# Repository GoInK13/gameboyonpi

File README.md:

# gameboyonpi

PCB in kicad directory.
Teensy software for joystick, mouse and media keyboard.

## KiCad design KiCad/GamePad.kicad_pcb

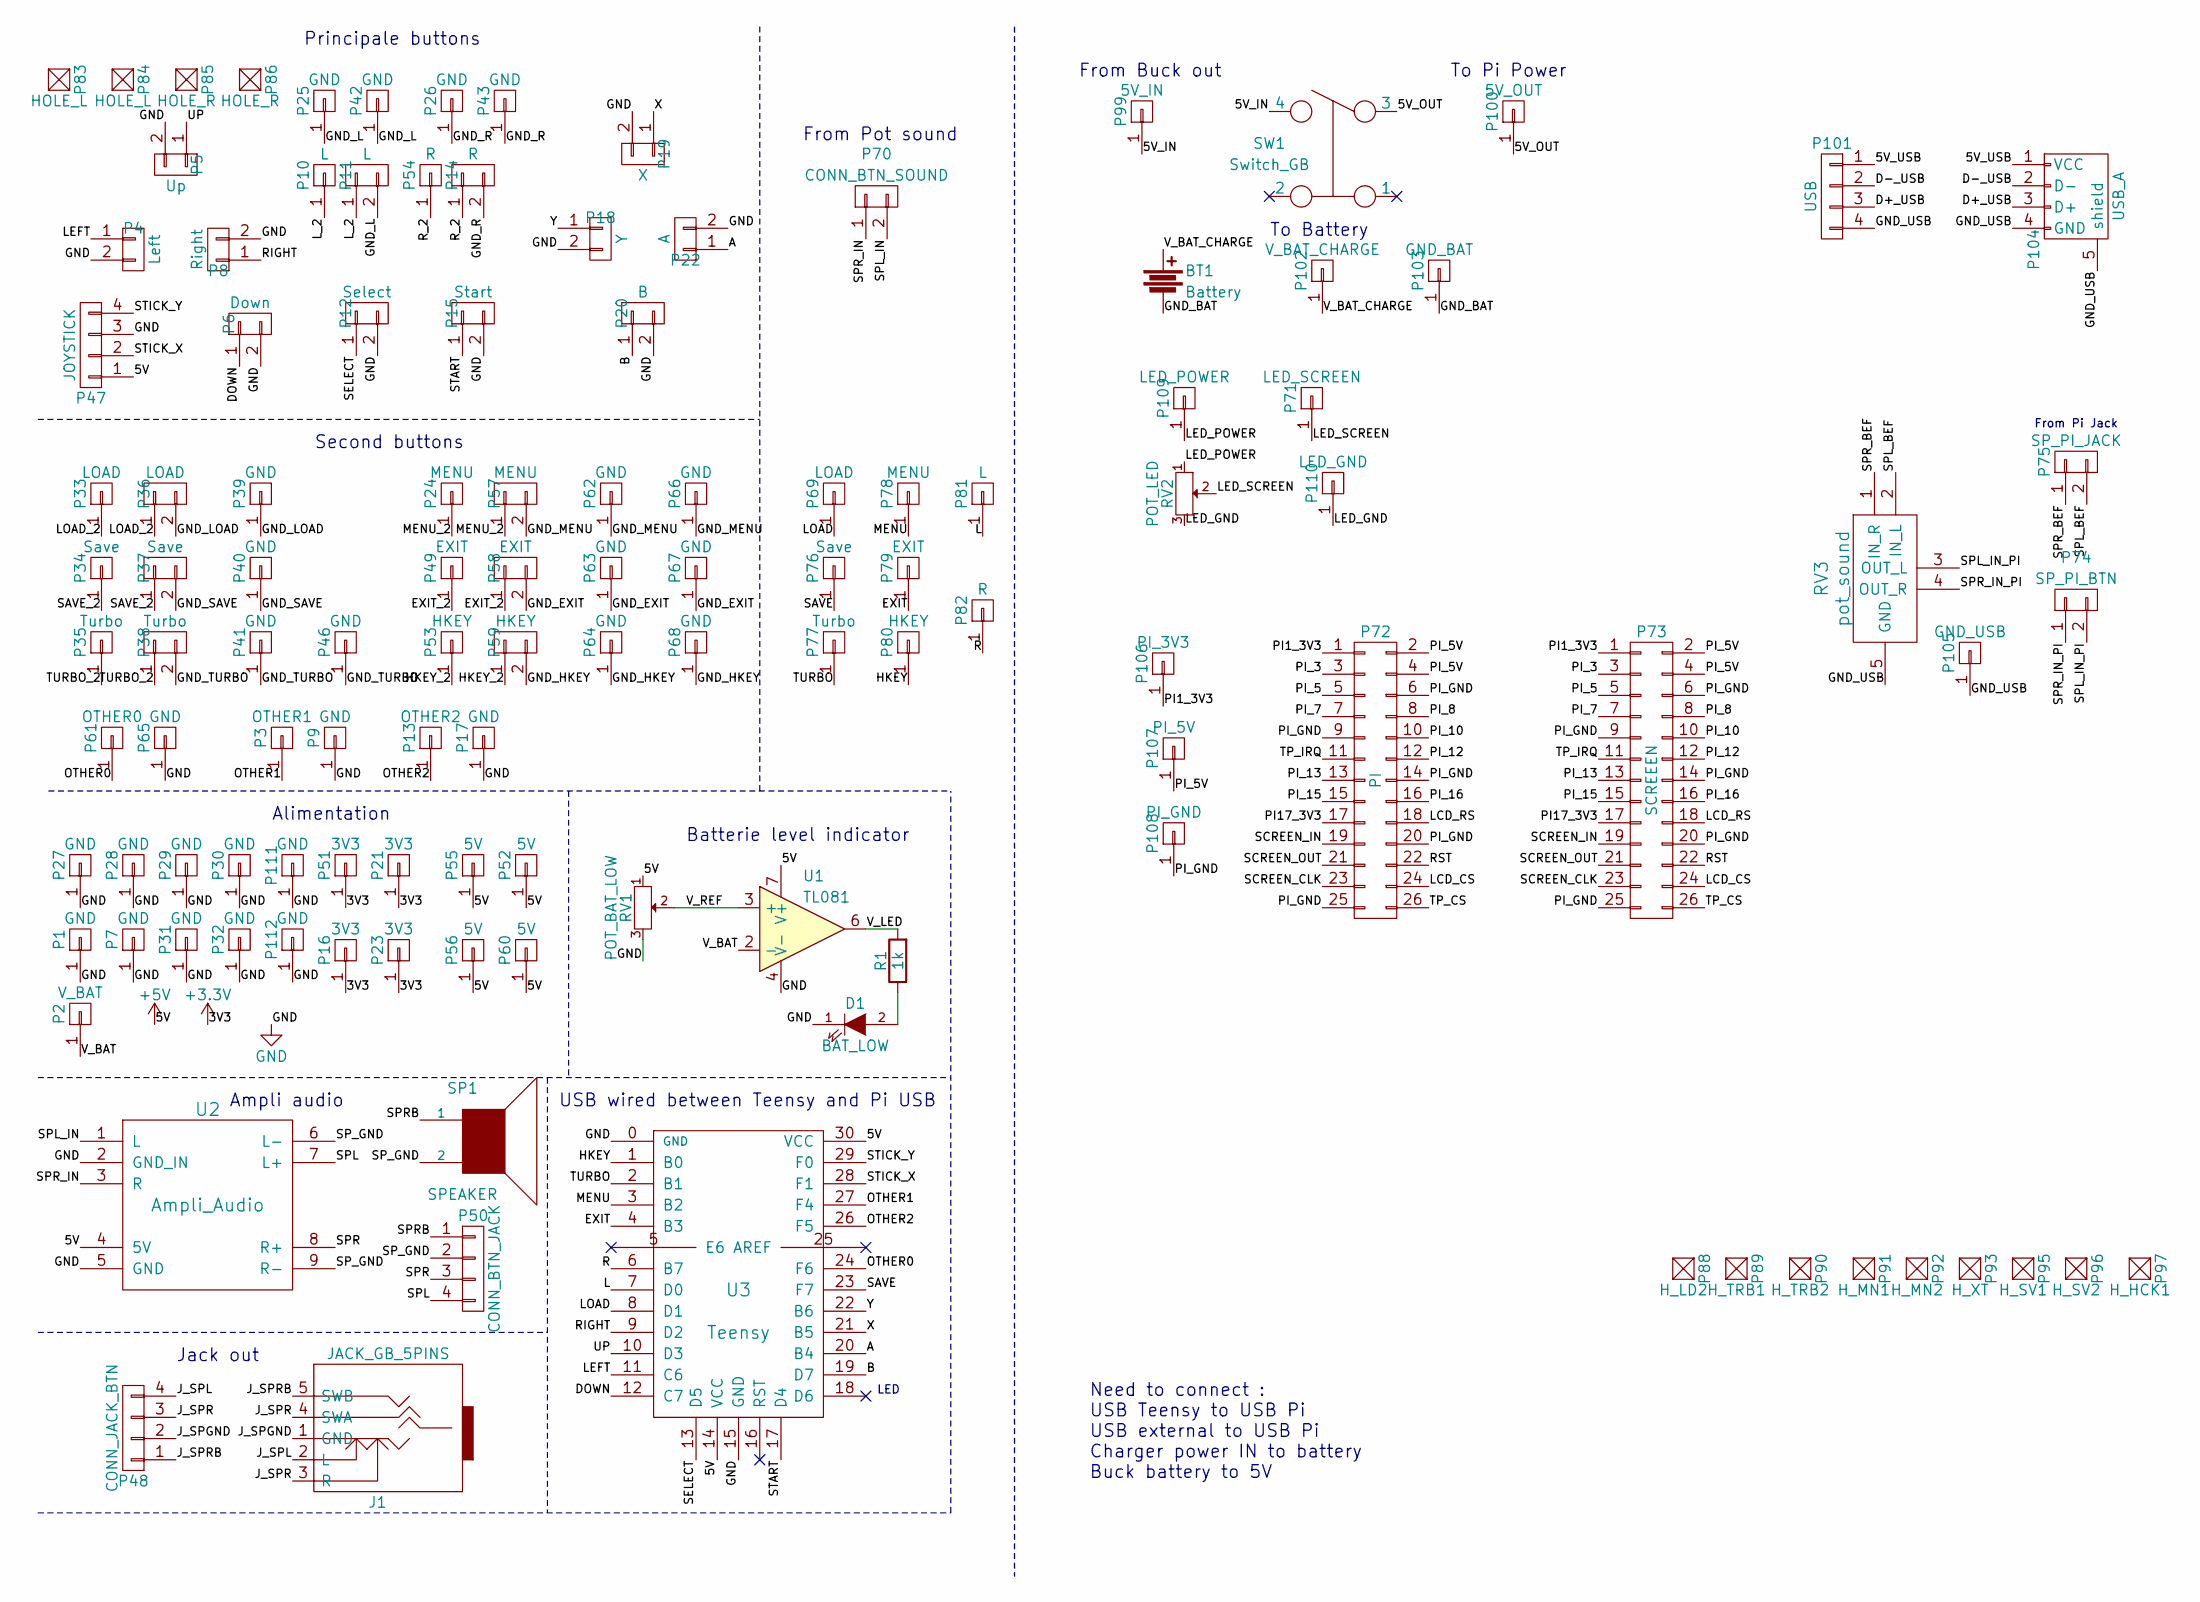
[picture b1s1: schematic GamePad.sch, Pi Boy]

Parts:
BT1: Battery; charger_bat
D1: BAT_LOW; LED-3MM
J1: JACK_GB_5PINS; Jack
P1, P7, P9, P17, P25, P26, P27, P28, P29, P30, P31, P32, P39, P40, P41, P42, P43, P46, P62, P63, P64, P65, P66, P67, P68, P111, P112: GND; header_1-2
P2: V_BAT; header_1-2
P3: OTHER1; header_1-2
P4: Left; button_round
P5: Up; button_round
P6: Down; button_round
P8: Right; button_round
P10, P81: L; header_1-2
P11: L; button_rectangle
P12: Select; button_rectangle
P13: OTHER2; header_1-2
P14: R; button_rectangle
P15: Start; button_rectangle
P16, P21, P23, P51: 3V3; header_1-2
P18: Y; button_round
P19: X; button_round
P20: B; button_round
P22: A; button_round
P24, P78: MENU; header_1-2
P33, P69: LOAD; header_1-2
P34, P76: Save; header_1-2
P35, P77: Turbo; header_1-2
P36: LOAD; button_round
P37: Save; button_round
P38: Turbo; button_round
P47: JOYSTICK; PSP_Joystick
P48: CONN_JACK_BTN; Pin_Header_Straight_1x04
P49, P79: EXIT; header_1-2
P50: CONN_BTN_JACK; Pin_Header_Straight_1x04
P52, P55, P56, P60: 5V; header_1-2
P53, P80: HKEY; header_1-2
P54, P82: R; header_1-2
P57: MENU; button_round
P58: EXIT; button_round
P59: HKEY; button_round
P61: OTHER0; header_1-2
P70: CONN_BTN_SOUND; Pin_Header_Straight_1x02
P71: LED_SCREEN; header_1-2
P72: PI; Socket_Strip_Straight_2x20
P73: SCREEEN; Socket_Strip_Straight_2x13
P74: SP_PI_BTN; Socket_Strip_Straight_1x02
P75: SP_PI_JACK; Pin_Header_Straight_1x02
P83, P84: HOLE_L; Hole_1mm
P85, P86: HOLE_R; Hole_1mm
P88: H_LD2; Hole_1mm
P89: H_TRB1; Hole_1mm
P90: H_TRB2; Hole_1mm
P91: H_MN1; Hole_1mm
P92: H_MN2; Hole_1mm
P93: H_XT; Hole_1mm
P95: H_SV1; Hole_1mm
P96: H_SV2; Hole_1mm
P97: H_HCK1; Hole_1mm
P99: 5V_IN; header_1-2
P100: 5V_OUT; header_1-2
P101: USB; Pin_Header_Straight_1x04
P102: V_BAT_CHARGE; header_1-2
P103: GND_BAT; header_1-2
P104: USB_A
P105: GND_USB; header_1-2
P106: PI_3V3; header_1-2
P107: PI_5V; header_1-2
P108: PI_GND; header_1-2
P109: LED_POWER; header_1-2
P110: LED_GND; header_1-2
R1: 1k; Resistor_Horizontal_RM10mm
RV1: POT_BAT_LOW; RV2X4
RV2: POT_LED; pot_screen
RV3: pot_sound
SP1: SPEAKER; Pin_Header_Straight_1x02
SW1: Switch_GB
U1: TL081; PDIP-8
U2: Ampli_Audio; ampli_audio
U3: Teensy

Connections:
+3V3: P16.1, P21.1, P23.1, P51.1
+5V: P47.1, P52.1, P55.1, P56.1, P60.1, RV1.1, U1.7 (V+), U2.4 (5V), U3.14 (VCC), U3.30 (VCC)
/5V_IN: P99.1, SW1.4
/5V_OUT: P100.1, SW1.3
/5V_USB: P101.1, P104.1 (VCC)
/A: P22.1, U3.20 (B4)
/B: P20.1, U3.19 (D7)
/D+_USB: P101.3, P104.3 (D+)
/D-_USB: P101.2, P104.2 (D-)
/DOWN: P6.1, U3.12 (C7)
/EXIT: P79.1, U3.4 (B3)
/EXIT_2: P49.1, P58.1
/GND_BAT: BT1.2, P103.1
/GND_EXIT: P58.2, P63.1, P67.1
/GND_HKEY: P59.2, P64.1, P68.1
/GND_L: P11.2, P25.1, P42.1
/GND_LOAD: P36.2, P39.1
/GND_MENU: P57.2, P62.1, P66.1
/GND_R: P14.2, P26.1, P43.1
/GND_SAVE: P37.2, P40.1
/GND_TURBO: P38.2, P41.1, P46.1
/GND_USB: P101.4, P104.4 (GND), P104.5 (shield), P105.1, RV3.5 (GND)
/HKEY: P80.1, U3.1 (B0)
/HKEY_2: P53.1, P59.1
/J_SPGND: J1.1 (GND), P48.2
/J_SPL: J1.2 (L), P48.4
/J_SPR: J1.3 (R), J1.4 (SWA), P48.3
/J_SPRB: J1.5 (SWB), P48.1
/L: P81.1, U3.7 (D0)
/LCD_CS: P72.24, P73.24
/LCD_RS: P72.18, P73.18
/LED_GND: P110.1, RV2.3
/LED_POWER: P109.1, RV2.1
/LED_SCREEN: P71.1, RV2.2
/LEFT: P4.1, U3.11 (C6)
/LOAD: P69.1, U3.8 (D1)
/LOAD_2: P33.1, P36.1
/L_2: P10.1, P11.1
/MENU: P78.1, U3.3 (B2)
/MENU_2: P24.1, P57.1
/OTHER0: P61.1, U3.24 (F6)
/OTHER1: P3.1, U3.27 (F4)
/OTHER2: P13.1, U3.26 (F5)
/PI1_3V3: P72.1, P73.1, P106.1
/PI17_3V3: P72.17, P73.17
/PI_3: P72.3, P73.3
/PI_5: P72.5, P73.5
/PI_5V: P72.2, P72.4, P73.2, P73.4, P107.1
/PI_7: P72.7, P73.7
/PI_8: P72.8, P73.8
/PI_10: P72.10, P73.10
/PI_12: P72.12, P73.12
/PI_13: P72.13, P73.13
/PI_15: P72.15, P73.15
/PI_16: P72.16, P73.16
/PI_GND: P72.6, P72.9, P72.14, P72.20, P72.25, P73.6, P73.9, P73.14, P73.20, P73.25, P108.1
/R: P82.1, U3.6 (B7)
/RIGHT: P8.1, U3.9 (D2)
/RST: P72.22, P73.22
/R_2: P14.1, P54.1
/SAVE: P76.1, U3.23 (F7)
/SAVE_2: P34.1, P37.1
/SCREEN_CLK: P72.23, P73.23
/SCREEN_IN: P72.19, P73.19
/SCREEN_OUT: P72.21, P73.21
/SELECT: P12.1, U3.13 (D5)
/SPL: P50.4, U2.7 (L+)
/SPL_BEF: P75.2, RV3.2 (IN_L)
/SPL_IN: P70.2, U2.1 (L)
/SPL_IN_PI: P74.2, RV3.3 (OUT_L)
/SPR: P50.3, U2.8 (R+)
/SPRB: P50.1, SP1.1
/SPR_BEF: P75.1, RV3.1 (IN_R)
/SPR_IN: P70.1, U2.3 (R)
/SPR_IN_PI: P74.1, RV3.4 (OUT_R)
/SP_GND: P50.2, SP1.2, U2.6 (L-), U2.9 (R-)
/START: P15.1, U3.17 (D4)
/STICK_X: P47.2, U3.28 (F1)
/STICK_Y: P47.4, U3.29 (F0)
/TP_CS: P72.26, P73.26
/TP_IRQ: P72.11, P73.11
/TURBO: P77.1, U3.2 (B1)
/TURBO_2: P35.1, P38.1
/UP: P5.1, U3.10 (D3)
/V_BAT: P2.1, U1.2 (-)
/V_BAT_CHARGE: BT1.1, P102.1
/V_LED: R1.2, U1.6
/V_REF: RV1.2, U1.3 (+)
/X: P19.1, U3.21 (B5)
/Y: P18.1, U3.22 (B6)
GND: D1.1 (K), P1.1, P4.2, P5.2, P6.2, P7.1, P8.2, P9.1, P12.2, P15.2, P17.1, P18.2, P19.2, P20.2, P22.2, P27.1, P28.1, P29.1, P30.1, P31.1, P32.1, P47.3, P65.1, P111.1, P112.1, RV1.3, U1.4 (V-), U2.2 (GND_IN), U2.5 (GND), U3.0 (GND), U3.15 (GND)
unnamed: D1.2 (A), R1.1

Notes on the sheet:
USB wired between Teensy and Pi USB
LED
From Pi Jack
Alimentation
Principale buttons
Second buttons
Ampli audio
Jack out
Batterie level indicator
Need to connect : USB Teensy to USB Pi USB external to USB Pi Charger power IN to battery Buck battery to 5V
From Buck out
To Pi Power
To Battery
From Pot sound

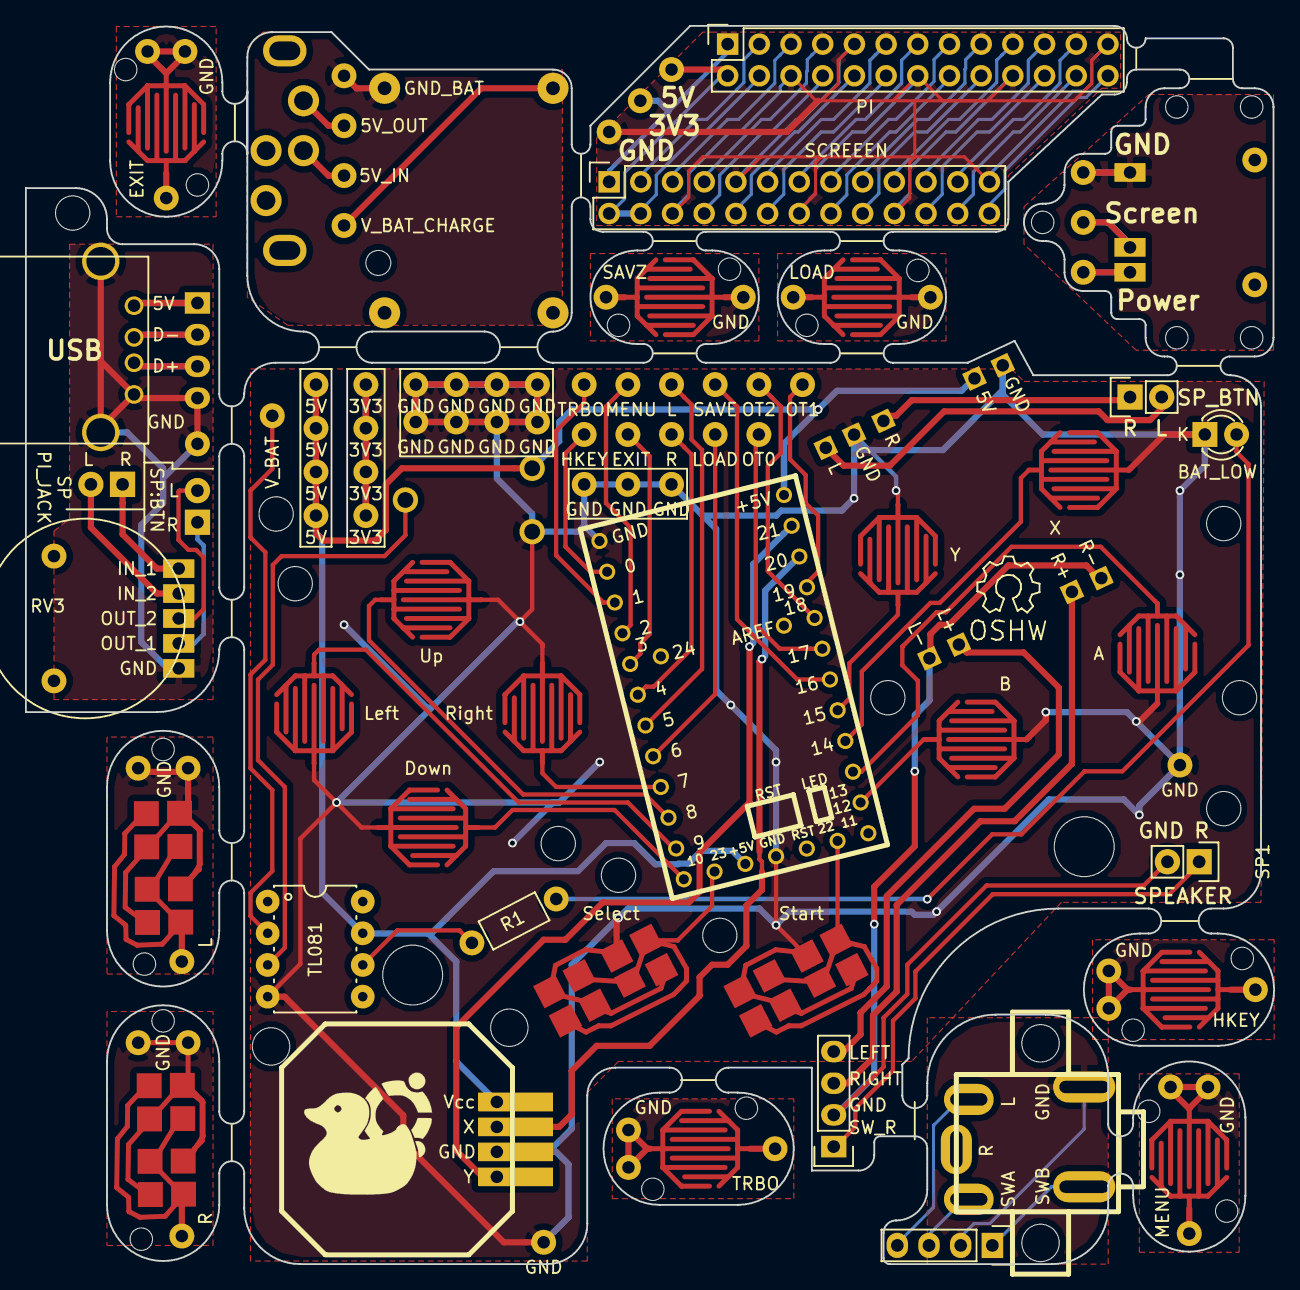
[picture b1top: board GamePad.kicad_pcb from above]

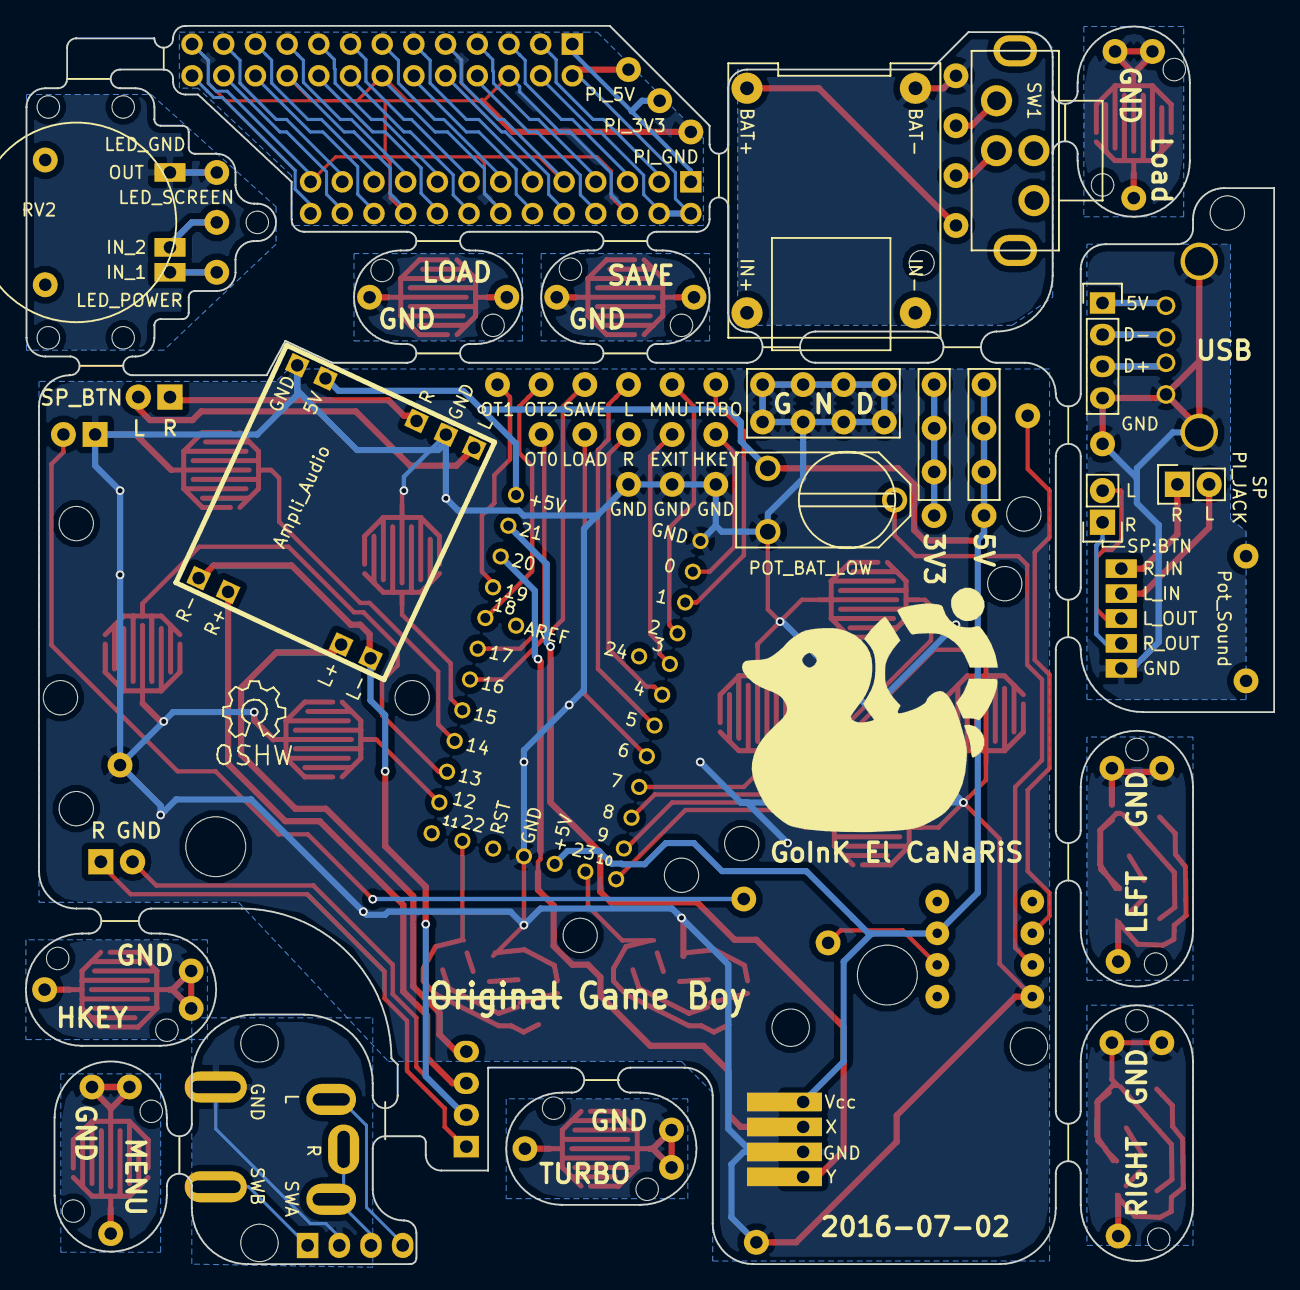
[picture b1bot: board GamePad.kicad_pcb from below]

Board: 2 copper layers, 100.1 x 99.2 mm, 127 parts (15 on the bottom side), 92 nets.

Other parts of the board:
P83#2, P83#3, P83#4, P83#5: HOLE_L; Hole_1mm
P93#2: H_XT; Hole_1mm
P95#2: H_SV1; Hole_1mm
P96#2, P96#3: H_SV2; Hole_1mm

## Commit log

2016-08-04 Create repo
2016-08-04 Remove useless files…
